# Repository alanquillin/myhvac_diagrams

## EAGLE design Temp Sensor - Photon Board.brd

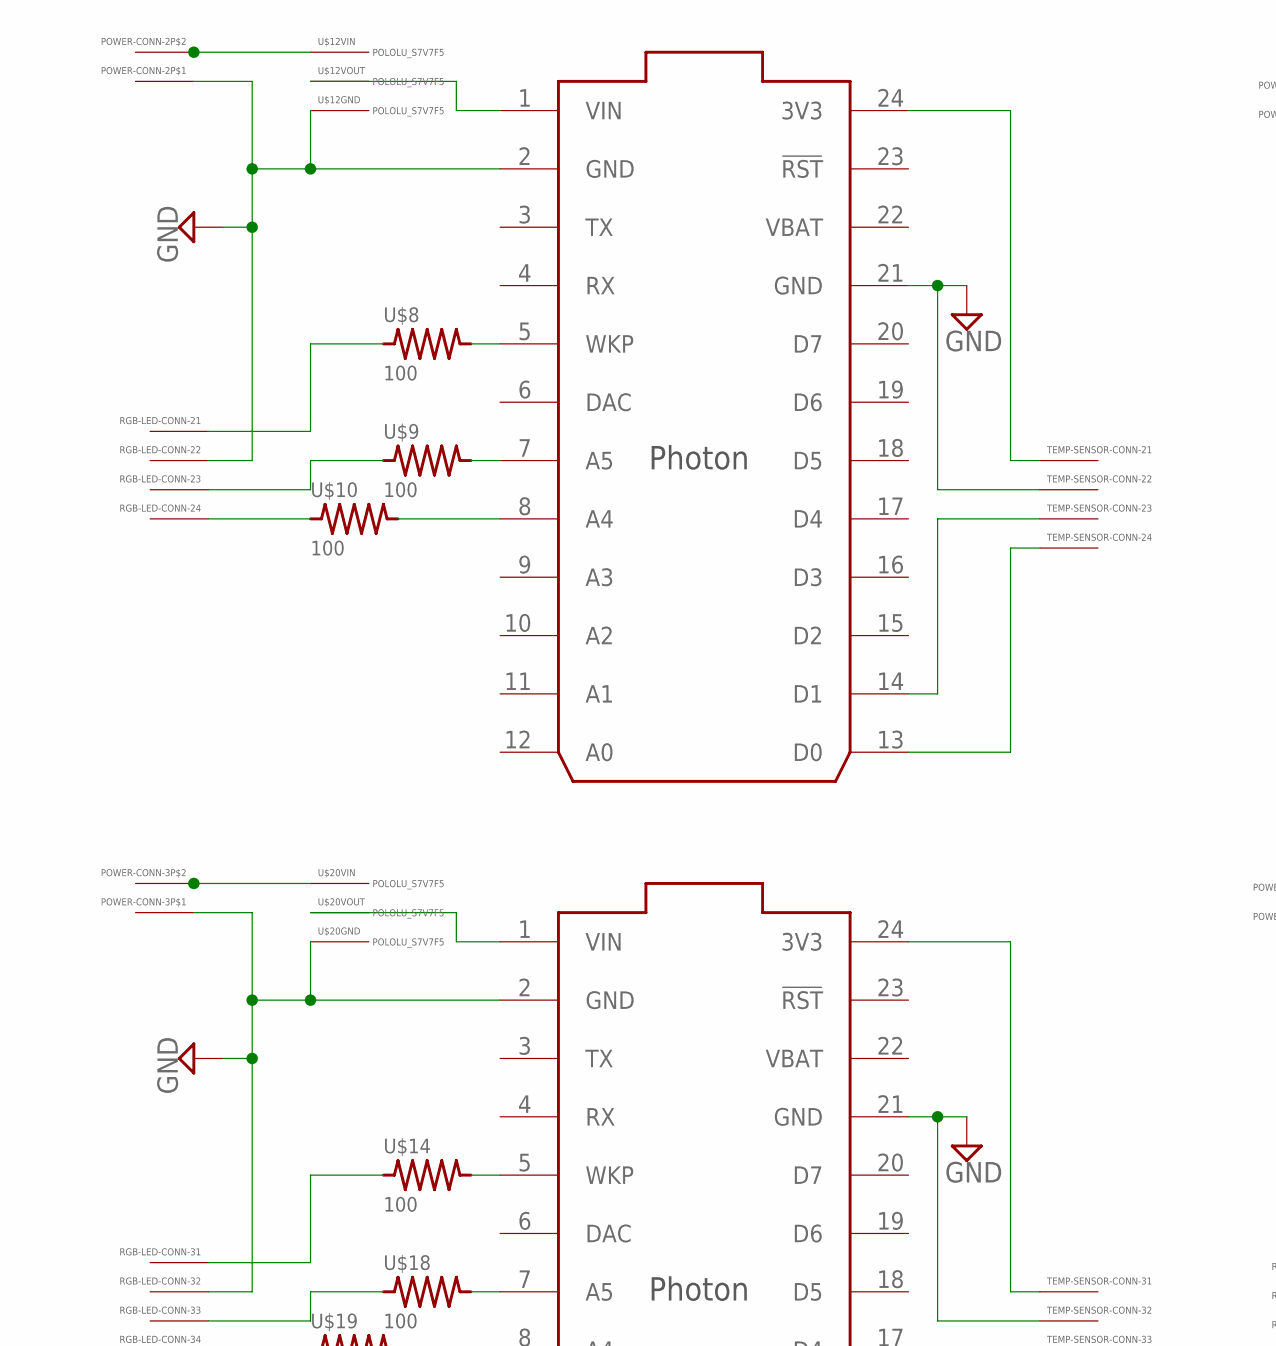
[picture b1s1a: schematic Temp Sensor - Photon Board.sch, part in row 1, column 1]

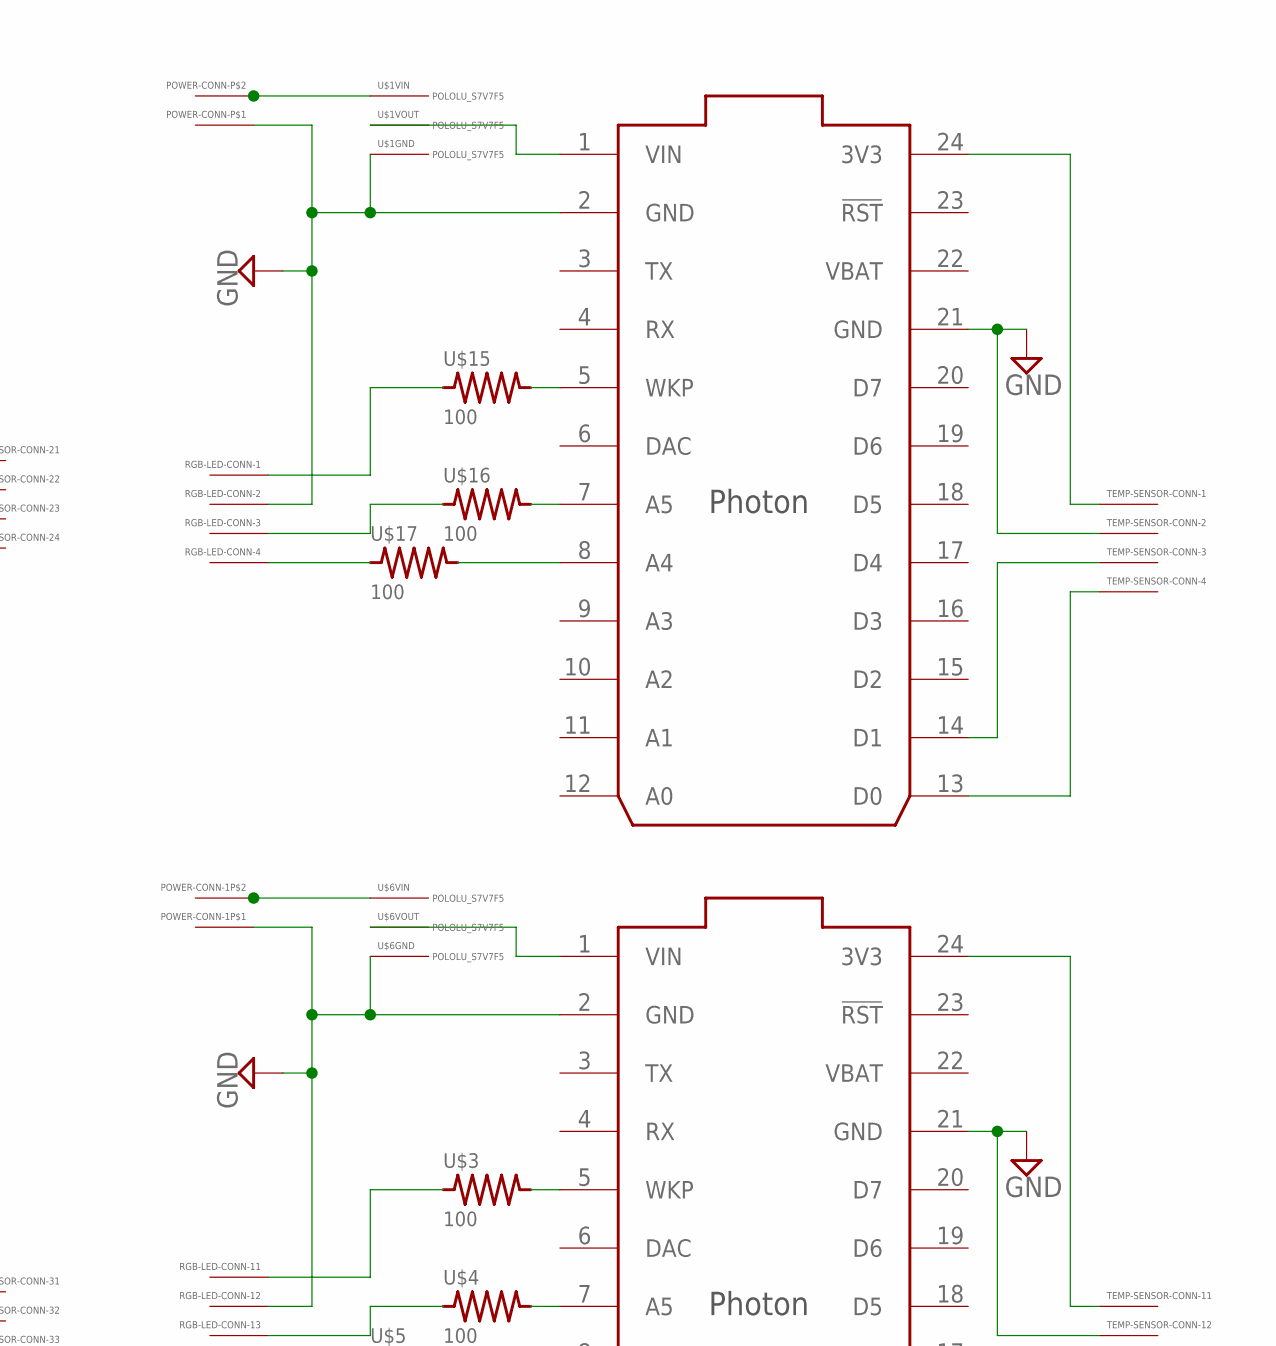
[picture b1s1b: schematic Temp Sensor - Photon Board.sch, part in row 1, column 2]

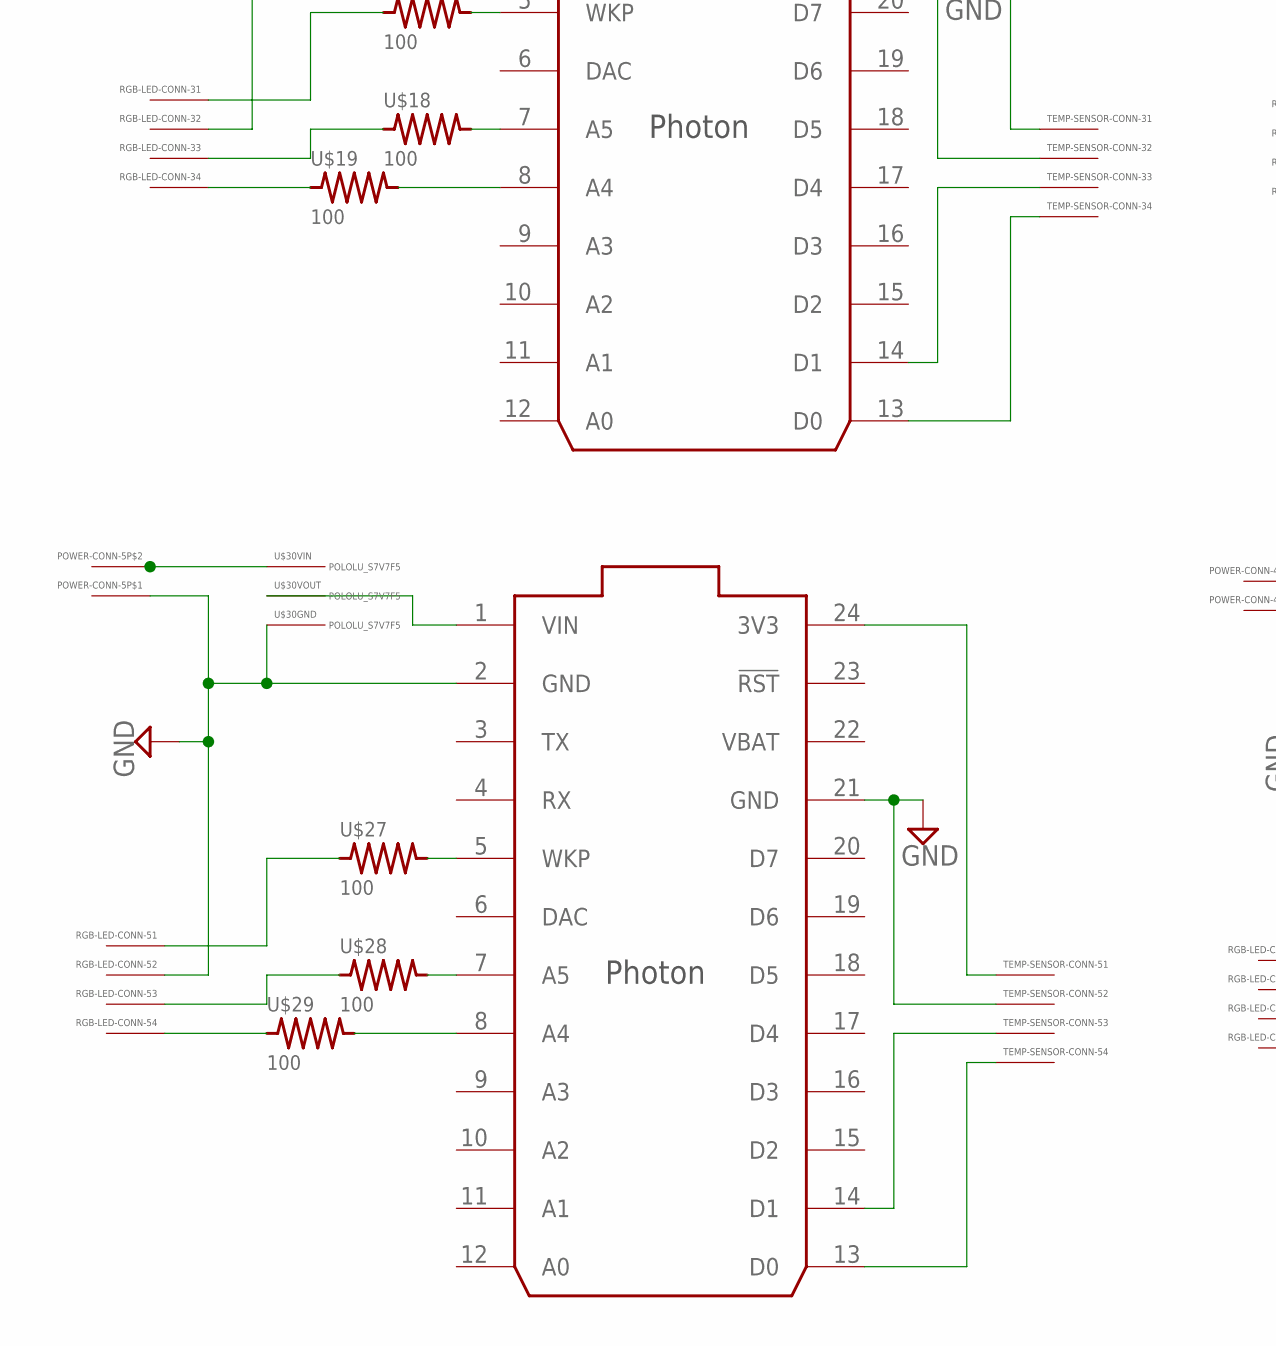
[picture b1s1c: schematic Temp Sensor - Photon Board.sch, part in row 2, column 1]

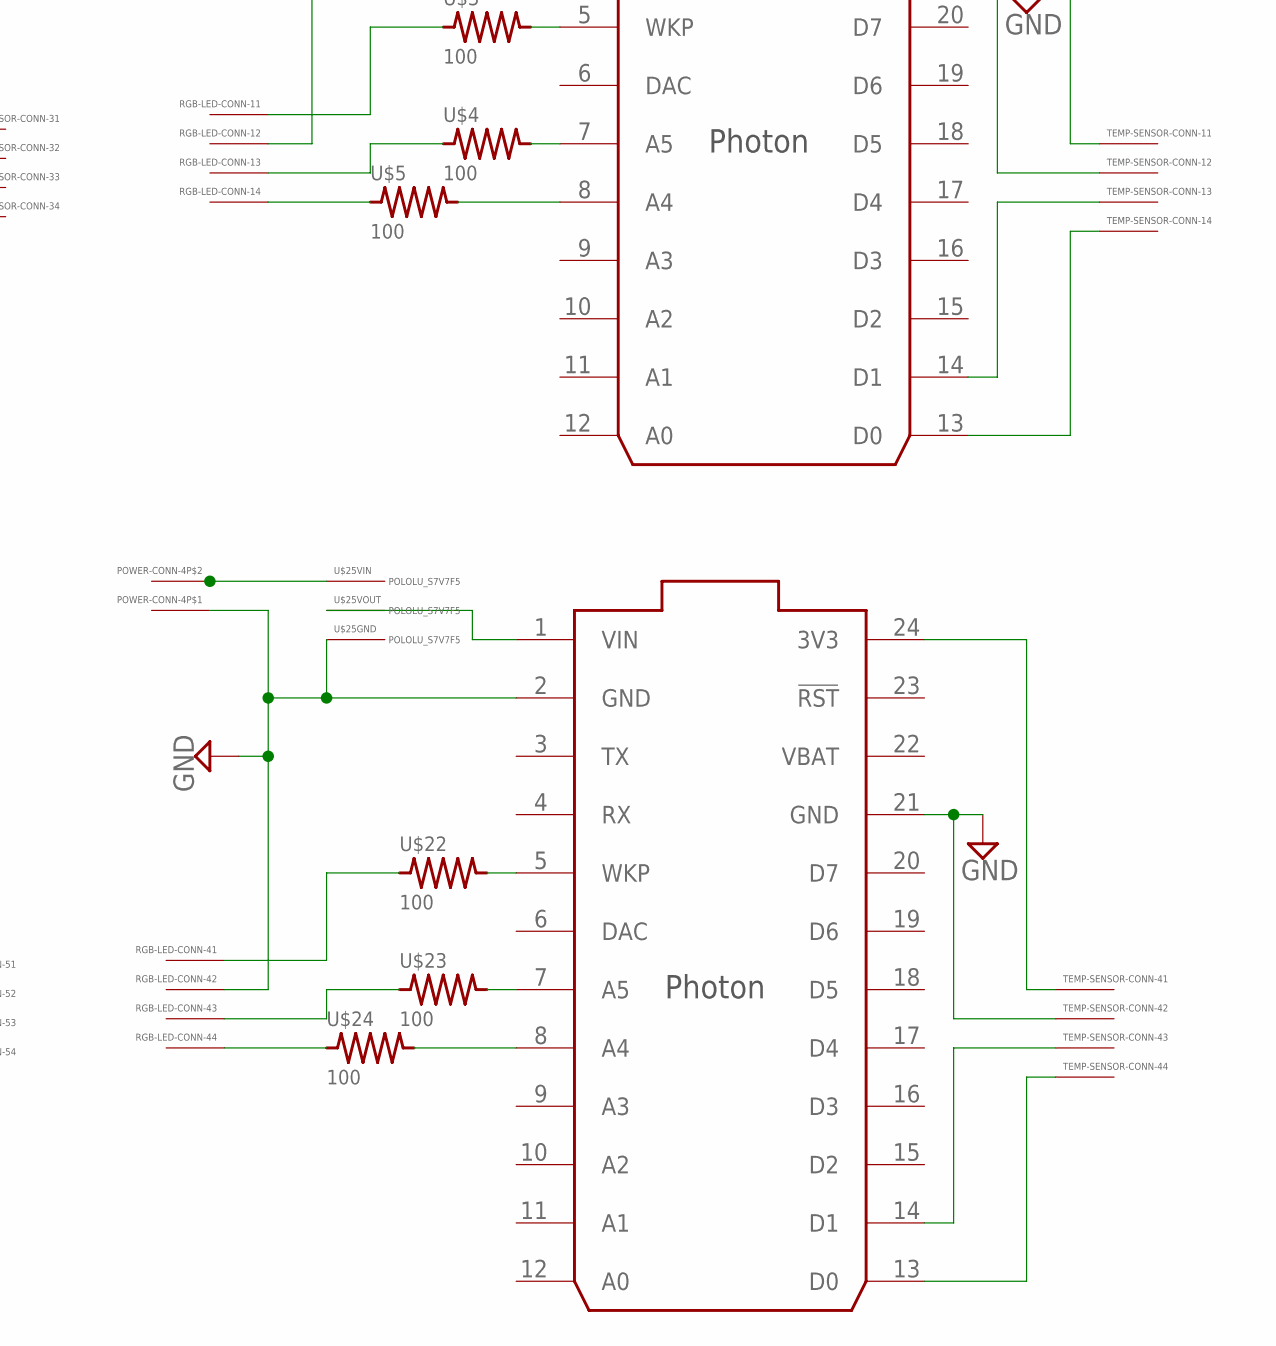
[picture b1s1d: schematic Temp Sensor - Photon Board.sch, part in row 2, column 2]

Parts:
POWER-CONN-, POWER-CONN-1, POWER-CONN-2, POWER-CONN-3, POWER-CONN-4, POWER-CONN-5: S2B-PH-K-S; JST_PH-2
RGB-LED-CONN-, RGB-LED-CONN-1, RGB-LED-CONN-2, RGB-LED-CONN-3, RGB-LED-CONN-4, RGB-LED-CONN-5: S4B-PH-K-S; JST_PH-4
TEMP-SENSOR-CONN-, TEMP-SENSOR-CONN-1, TEMP-SENSOR-CONN-2, TEMP-SENSOR-CONN-3, TEMP-SENSOR-CONN-4, TEMP-SENSOR-CONN-5: S4B-PH-K-S; JST_PH-4
U$1, U$6, U$12, U$20, U$25, U$30: POLOLU_S7V7F5; S7V7F5
U$2, U$7, U$11, U$13, U$21, U$26: Photon w/ Headers; PHOTON
U$3, U$4, U$5, U$8, U$9, U$10, U$14, U$15, U$16, U$17, U$18, U$19, U$22, U$23, U$24, U$27, U$28, U$29: 100; R0805

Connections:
GND: POWER-CONN-.P$1, POWER-CONN-1.P$1, POWER-CONN-2.P$1, POWER-CONN-3.P$1, POWER-CONN-4.P$1, POWER-CONN-5.P$1, RGB-LED-CONN-.P$2, RGB-LED-CONN-1.P$2, RGB-LED-CONN-2.P$2, RGB-LED-CONN-3.P$2, RGB-LED-CONN-4.P$2, RGB-LED-CONN-5.P$2, TEMP-SENSOR-CONN-.P$2, TEMP-SENSOR-CONN-1.P$2, TEMP-SENSOR-CONN-2.P$2, TEMP-SENSOR-CONN-3.P$2, TEMP-SENSOR-CONN-4.P$2, TEMP-SENSOR-CONN-5.P$2, U$1.GND, U$2.2 (GND), U$2.21 (GND), U$6.GND, U$7.2 (GND), U$7.21 (GND), U$11.2 (GND), U$11.21 (GND), U$12.GND, U$13.2 (GND), U$13.21 (GND), U$20.GND, U$21.2 (GND), U$21.21 (GND), U$25.GND, U$26.2 (GND), U$26.21 (GND), U$30.GND
unnamed: U$11.5 (WKP), U$15.2
unnamed: RGB-LED-CONN-.P$3, U$16.1
unnamed: RGB-LED-CONN-.P$4, U$17.1
unnamed: U$1.VOUT, U$11.1 (VIN)
unnamed: POWER-CONN-.P$2, U$1.VIN
unnamed: RGB-LED-CONN-1.P$3, U$4.1
unnamed: TEMP-SENSOR-CONN-.P$1, U$11.24 (3V3)
unnamed: TEMP-SENSOR-CONN-.P$3, U$11.14 (D1)
unnamed: TEMP-SENSOR-CONN-.P$4, U$11.13 (D0)
unnamed: RGB-LED-CONN-1.P$4, U$5.1
unnamed: U$11.7 (A5), U$16.2
unnamed: U$11.8 (A4), U$17.2
unnamed: RGB-LED-CONN-.P$1, U$15.1
unnamed: TEMP-SENSOR-CONN-1.P$1, U$2.24 (3V3)
unnamed: TEMP-SENSOR-CONN-1.P$3, U$2.14 (D1)
unnamed: TEMP-SENSOR-CONN-1.P$4, U$2.13 (D0)
unnamed: U$2.5 (WKP), U$3.2
unnamed: U$2.7 (A5), U$4.2
unnamed: U$2.8 (A4), U$5.2
unnamed: RGB-LED-CONN-1.P$1, U$3.1
unnamed: U$2.1 (VIN), U$6.VOUT
unnamed: POWER-CONN-1.P$2, U$6.VIN
unnamed: RGB-LED-CONN-2.P$3, U$9.1
unnamed: RGB-LED-CONN-2.P$4, U$10.1
unnamed: TEMP-SENSOR-CONN-2.P$1, U$7.24 (3V3)
unnamed: TEMP-SENSOR-CONN-2.P$3, U$7.14 (D1)
unnamed: TEMP-SENSOR-CONN-2.P$4, U$7.13 (D0)
unnamed: U$7.5 (WKP), U$8.2
unnamed: U$7.7 (A5), U$9.2
unnamed: U$7.8 (A4), U$10.2
unnamed: RGB-LED-CONN-2.P$1, U$8.1
unnamed: U$7.1 (VIN), U$12.VOUT
unnamed: POWER-CONN-2.P$2, U$12.VIN
unnamed: RGB-LED-CONN-3.P$3, U$18.1
unnamed: RGB-LED-CONN-3.P$4, U$19.1
unnamed: TEMP-SENSOR-CONN-3.P$1, U$13.24 (3V3)
unnamed: TEMP-SENSOR-CONN-3.P$3, U$13.14 (D1)
unnamed: TEMP-SENSOR-CONN-3.P$4, U$13.13 (D0)
unnamed: U$13.5 (WKP), U$14.2
unnamed: U$13.7 (A5), U$18.2
unnamed: U$13.8 (A4), U$19.2
unnamed: RGB-LED-CONN-3.P$1, U$14.1
unnamed: U$13.1 (VIN), U$20.VOUT
unnamed: POWER-CONN-3.P$2, U$20.VIN
unnamed: RGB-LED-CONN-4.P$3, U$23.1
unnamed: RGB-LED-CONN-4.P$4, U$24.1
unnamed: TEMP-SENSOR-CONN-4.P$1, U$21.24 (3V3)
unnamed: TEMP-SENSOR-CONN-4.P$3, U$21.14 (D1)
unnamed: TEMP-SENSOR-CONN-4.P$4, U$21.13 (D0)
unnamed: U$21.5 (WKP), U$22.2
unnamed: U$21.7 (A5), U$23.2
unnamed: U$21.8 (A4), U$24.2
unnamed: RGB-LED-CONN-4.P$1, U$22.1
unnamed: U$21.1 (VIN), U$25.VOUT
unnamed: POWER-CONN-4.P$2, U$25.VIN
unnamed: RGB-LED-CONN-5.P$3, U$28.1
unnamed: RGB-LED-CONN-5.P$4, U$29.1
unnamed: TEMP-SENSOR-CONN-5.P$1, U$26.24 (3V3)
unnamed: TEMP-SENSOR-CONN-5.P$3, U$26.14 (D1)
unnamed: TEMP-SENSOR-CONN-5.P$4, U$26.13 (D0)
unnamed: U$26.5 (WKP), U$27.2
unnamed: U$26.7 (A5), U$28.2
unnamed: U$26.8 (A4), U$29.2
unnamed: RGB-LED-CONN-5.P$1, U$27.1
unnamed: U$26.1 (VIN), U$30.VOUT
unnamed: POWER-CONN-5.P$2, U$30.VIN
VBAT: U$2.22 (VBAT), U$7.22 (VBAT), U$11.22 (VBAT), U$13.22 (VBAT), U$21.22 (VBAT), U$26.22 (VBAT)

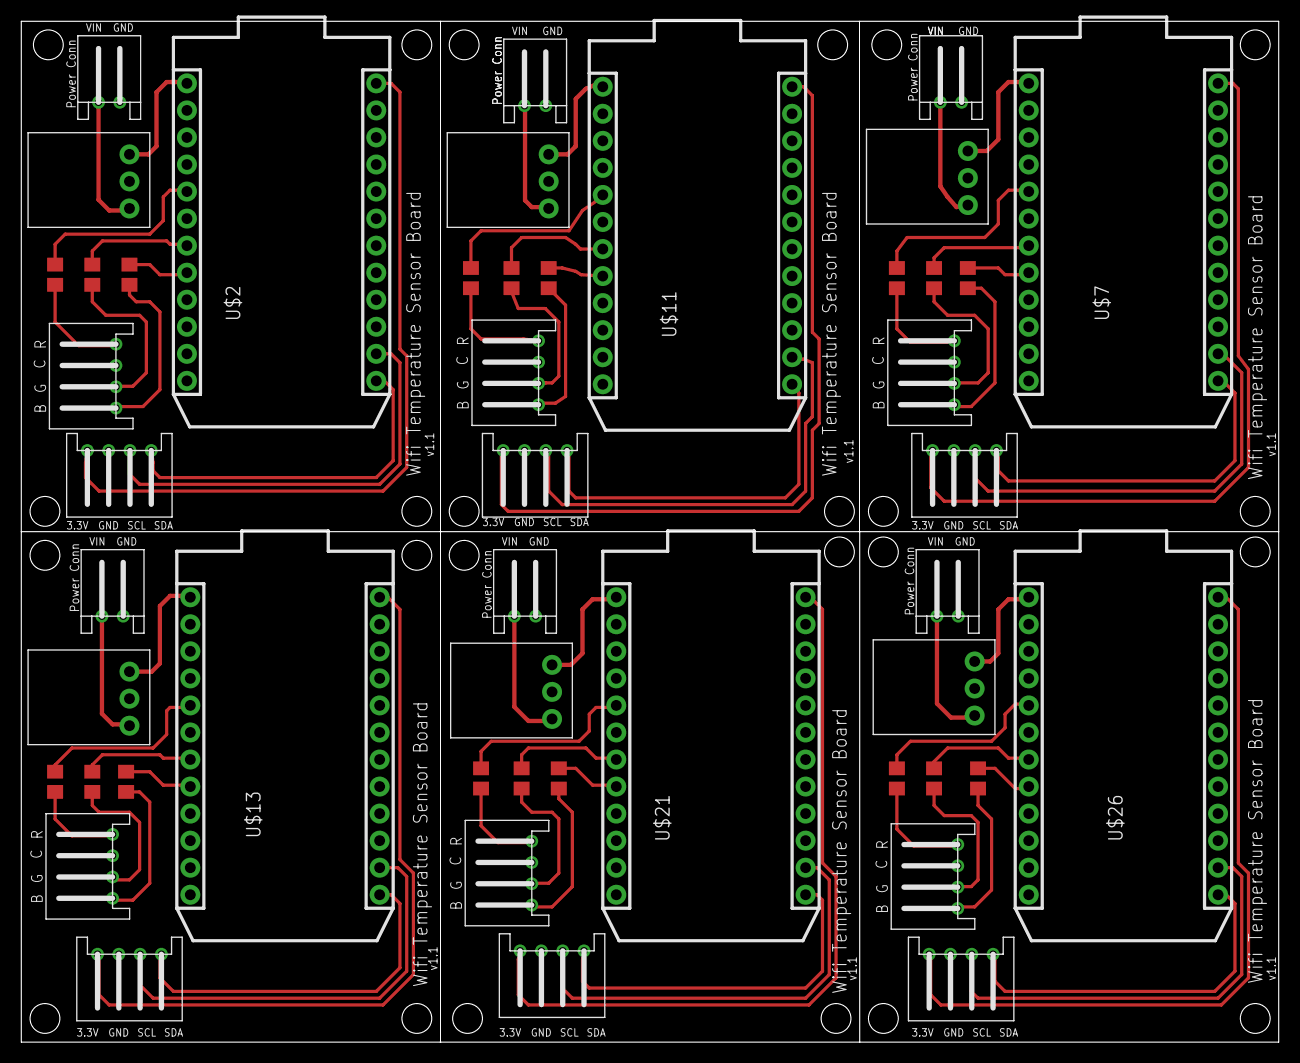
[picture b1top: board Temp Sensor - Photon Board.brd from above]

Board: 2 copper layers, 118.1 x 95.9 mm, 48 parts (0 on the bottom side), 68 nets.

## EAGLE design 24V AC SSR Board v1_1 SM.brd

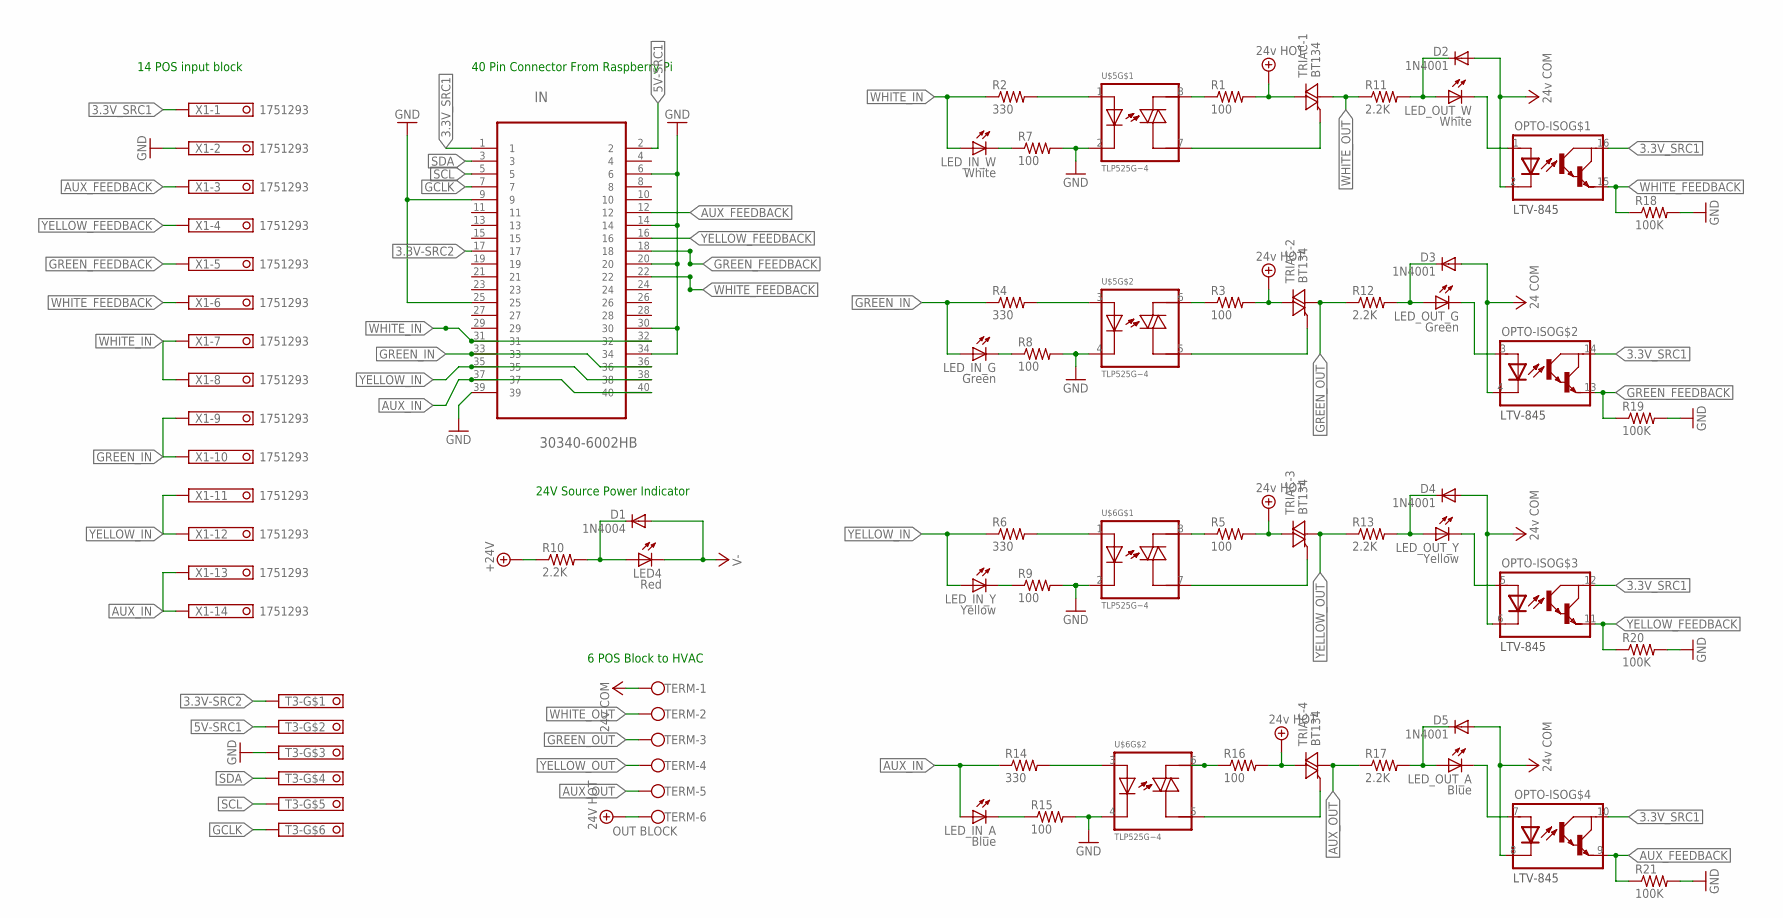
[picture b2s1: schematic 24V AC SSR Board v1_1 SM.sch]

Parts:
D1: 1N4004; DO41-10
D2, D3, D4, D5: 1N4001; DO41-10
IN: 30340-6002HB; 3M_2540-6002UB
LED4: Red; LED3MM
LED_IN_A: Blue; LED3MM
LED_IN_G: Green; LED3MM
LED_IN_W: White; LED3MM
LED_IN_Y: Yellow; LED3MM
LED_OUT_A: Blue; LED3MM
LED_OUT_G: Green; LED3MM
LED_OUT_W: White; LED3MM
LED_OUT_Y: Yellow; LED3MM
OPTO-ISO: LTV-845; DIL16
R1, R3, R5, R7, R8, R9, R15, R16: 100; 0204/7
R2, R4, R6, R14: 330; 0204/7
R10, R11, R12, R13, R17: 2.2K; 0204/7
R18, R19, R20, R21: 100K; 0204/7
T3-: 6-POS-SCREW-TERM-PT-3.5MM
TERM: OUT BLOCK; W237-6
TRIAC-1, TRIAC-2, TRIAC-3, TRIAC-4: BT134; SOT82
U$5, U$6: TLP525G−4; DIL08
X1: 1751293

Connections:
3.3V-SRC2: IN.17, T3-.1
3.3V_SRC1: IN.1, OPTO-ISO.10 (COLLECTOR), OPTO-ISO.12 (COLLECTOR), OPTO-ISO.14 (COLLECTOR), OPTO-ISO.16 (COLLECTOR), X1.1
5V-SRC1: IN.2, T3-.2
+24V: R1.2, R3.2, R5.2, R10.1, R16.2, TERM.6, TRIAC-1.2 (A2), TRIAC-2.2 (A2), TRIAC-3.2 (A2), TRIAC-4.2 (A2)
AUX_FEEDBACK: IN.12, OPTO-ISO.9 (EMITTER), R21.1, X1.3
AUX_IN: IN.37, IN.40, LED_IN_A.A, R14.1, X1.13, X1.14
AUX_OUT: R17.1, TERM.5, TRIAC-4.1 (A1)
GCLK: IN.7, T3-.6
GND: IN.6, IN.9, IN.14, IN.20, IN.25, IN.30, IN.34, IN.39, R7.2, R8.2, R9.2, R15.2, R18.2, R19.2, R20.2, R21.2, T3-.3, U$5.2 (CATHODE), U$5.4 (CATHODE), U$6.2 (CATHODE), U$6.4 (CATHODE), X1.2
GREEN_FEEDBACK: IN.18, OPTO-ISO.13 (EMITTER), R19.1, X1.5
GREEN_IN: IN.33, IN.36, LED_IN_G.A, R4.1, X1.9, X1.10
GREEN_OUT: R12.1, TERM.3, TRIAC-2.1 (A1)
unnamed: TRIAC-1.3 (G), U$5.7 (T1)
unnamed: R2.2, U$5.1 (ANNODE)
unnamed: TRIAC-4.3 (G), U$6.5 (T1)
unnamed: R1.1, U$5.8 (T2)
unnamed: TRIAC-3.3 (G), U$6.7 (T1)
unnamed: R4.2, U$5.3 (ANNODE)
unnamed: TRIAC-2.3 (G), U$5.5 (T1)
unnamed: R3.1, U$5.6 (T2)
unnamed: LED_OUT_W.K (C), OPTO-ISO.1 (ANNODE)
unnamed: R6.2, U$6.1 (ANNODE)
unnamed: LED_OUT_G.K (C), OPTO-ISO.3 (ANNODE)
unnamed: R5.1, U$6.8 (T2)
unnamed: LED_OUT_Y.K (C), OPTO-ISO.5 (ANNODE)
unnamed: LED_OUT_A.K (C), OPTO-ISO.7 (ANNODE)
unnamed: LED_IN_W.K (C), R7.1
unnamed: LED_IN_G.K (C), R8.1
unnamed: LED_IN_Y.K (C), R9.1
unnamed: D2.C, LED_OUT_W.A, R11.2
unnamed: D3.C, LED_OUT_G.A, R12.2
unnamed: D4.C, LED_OUT_Y.A, R13.2
unnamed: D1.C, LED4.A, R10.2
unnamed: R14.2, U$6.3 (ANNODE)
unnamed: LED_IN_A.K (C), R15.1
unnamed: R16.1, U$6.6 (T2)
unnamed: D5.C, LED_OUT_A.A, R17.2
SCL: IN.5, T3-.5
SDA: IN.3, T3-.4
V-: D1.A, D2.A, D3.A, D4.A, D5.A, LED4.K (C), OPTO-ISO.2 (CATHODE), OPTO-ISO.4 (CATHODE), OPTO-ISO.6 (CATHODE), OPTO-ISO.8 (CATHODE), TERM.1
WHITE_FEEDBACK: IN.22, OPTO-ISO.15 (EMITTER), R18.1, X1.6
WHITE_IN: IN.31, IN.32, LED_IN_W.A, R2.1, X1.7, X1.8
WHITE_OUT: R11.1, TERM.2, TRIAC-1.1 (A1)
YELLOW_FEEDBACK: IN.16, OPTO-ISO.11 (EMITTER), R20.1, X1.4
YELLOW_IN: IN.35, IN.38, LED_IN_Y.A, R6.1, X1.11, X1.12
YELLOW_OUT: R13.1, TERM.4, TRIAC-3.1 (A1)

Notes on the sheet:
40 Pin Connector From Raspberry Pi
6 POS Block to HVAC
24V Source Power Indicator
14 POS input block

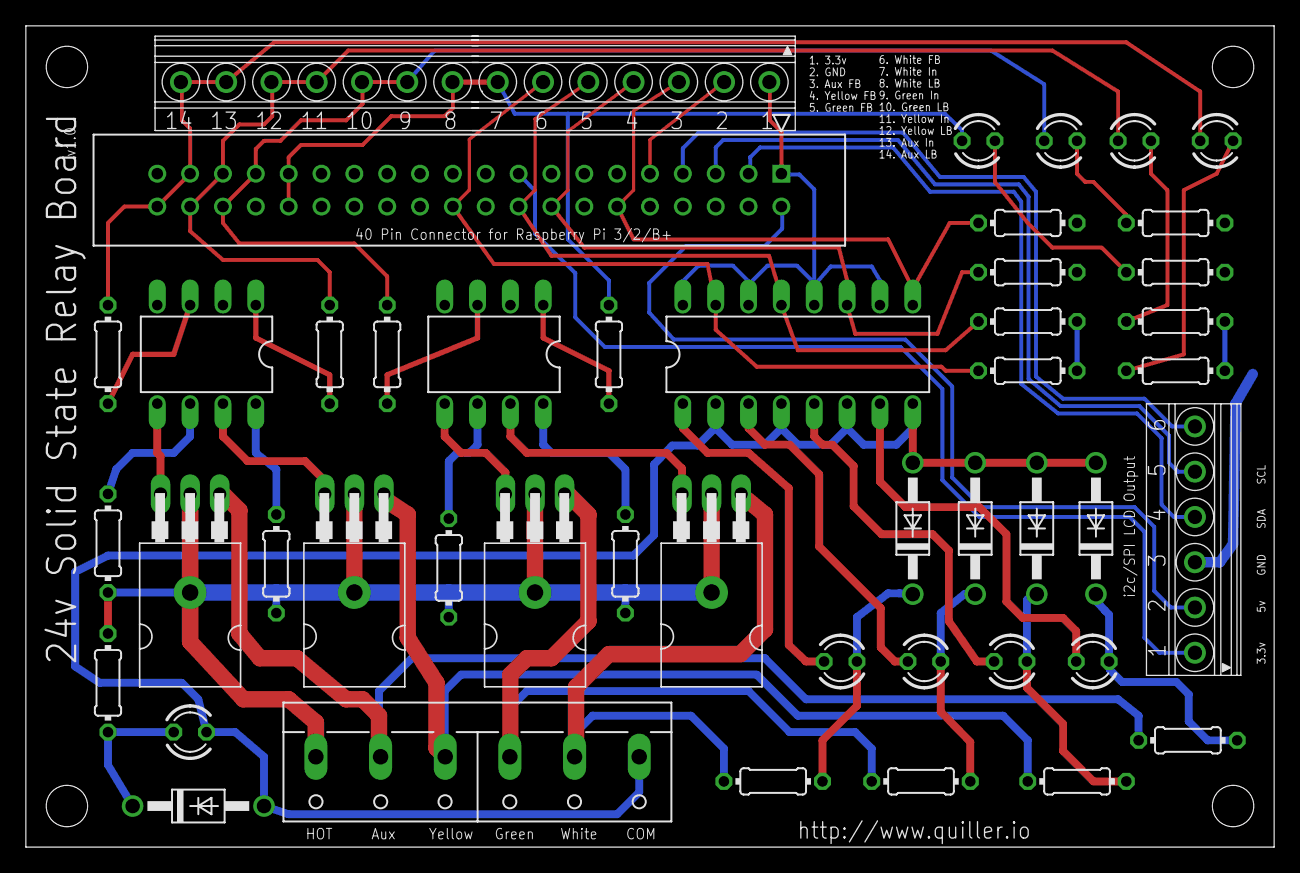
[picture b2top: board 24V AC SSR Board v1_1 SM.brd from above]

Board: 2 copper layers, 96.5 x 63.5 mm, 46 parts (0 on the bottom side), 46 nets.

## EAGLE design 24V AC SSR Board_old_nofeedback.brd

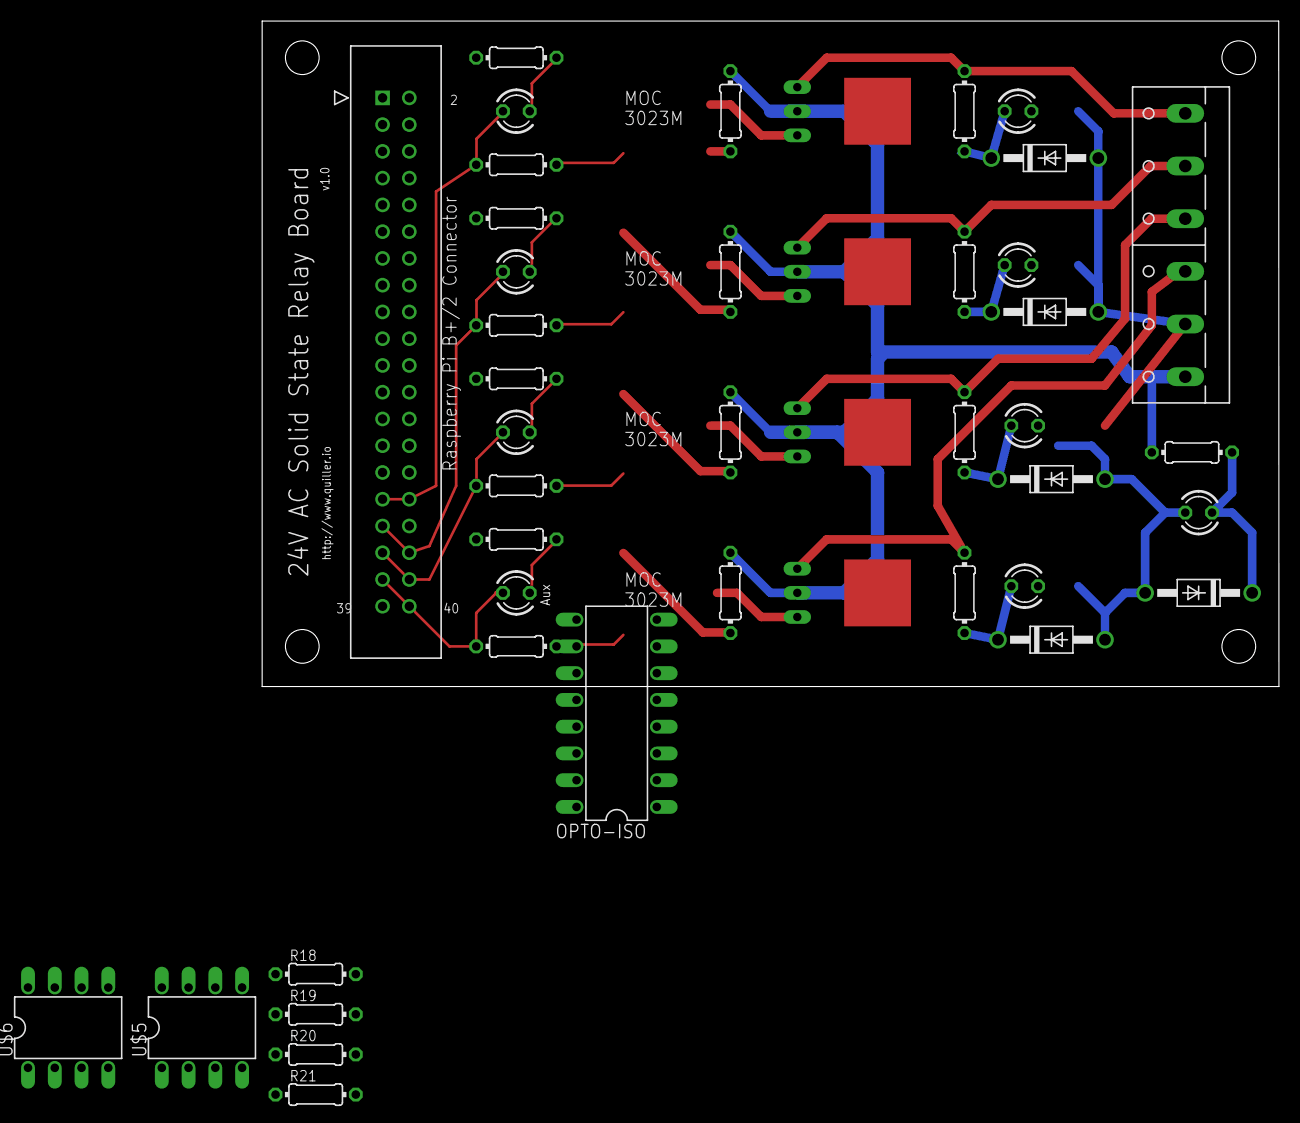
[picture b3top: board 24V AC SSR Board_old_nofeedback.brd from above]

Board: 2 copper layers, 96.5 x 63.2 mm, 44 parts (0 on the bottom side), 41 nets.

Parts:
D1: 1N4004; DO41-10
D2, D3, D4, D5: 1N4001; DO41-10
IN: 30340-6002HB; 3M_2540-6002UB
LED1, LED5: White; LED3MM
LED2, LED6: Green; LED3MM
LED3, LED7: Yellow; LED3MM
LED4: red; LED3MM
LED8, LED9: Blue; LED3MM
OPTO-ISO: LTV-845; DIL16
R1, R3, R5, R16: 100; 0204/7
R2, R4, R6, R14: 330; 0204/7
R7, R8, R9, R15: 56; 0204/7
R10, R11, R12, R13, R17: 2.2K; 0204/7
R18, R19, R20, R21: 4.7K; 0204/7
TERM: W237-6
U$1, U$2, U$3, U$4: BT134; SOT-82
U$5, U$6: TLP525G−4; DIL08

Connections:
3.3V_SOURCE: IN.1, OPTO-ISO.10, OPTO-ISO.12, OPTO-ISO.14, OPTO-ISO.16
+24V: R1.2, R3.2, R5.2, R10.1, R16.2, TERM.1, U$1.P$2, U$2.P$2, U$3.P$2, U$4.P$2
AUX_IN: IN.37, IN.40, LED8.A, R14.1
AUX_LOOPBACK: IN.22, OPTO-ISO.9, R21.1
AUX_OUT: R17.1, TERM.3, U$4.P$1
GND: IN.6, IN.9, IN.14, IN.20, IN.25, IN.30, IN.34, IN.39, R7.2, R8.2, R9.2, R15.2, R18.2, R19.2, R20.2, R21.2, U$5.2, U$5.4, U$6.2, U$6.4
GREEN_IN: IN.33, IN.36, LED2.A, R4.1
GREEN_LOOPBACK: IN.16, OPTO-ISO.13, R19.1
GREEN_OUT: R12.1, TERM.5, U$2.P$1
unnamed: U$1.P$3, U$5.7
unnamed: R2.2, U$5.1
unnamed: U$4.P$3, U$6.5
unnamed: R1.1, U$5.8
unnamed: U$3.P$3, U$6.7
unnamed: R4.2, U$5.3
unnamed: U$2.P$3, U$5.5
unnamed: R3.1, U$5.6
unnamed: LED5.K, OPTO-ISO.1
unnamed: R6.2, U$6.1
unnamed: LED6.K, OPTO-ISO.3
unnamed: R5.1, U$6.8
unnamed: LED7.K, OPTO-ISO.5
unnamed: LED9.K, OPTO-ISO.7
unnamed: LED1.K, R7.1
unnamed: LED2.K, R8.1
unnamed: LED3.K, R9.1
unnamed: D2.C, LED5.A, R11.2
unnamed: D3.C, LED6.A, R12.2
unnamed: D4.C, LED7.A, R13.2
unnamed: D1.C, LED4.A, R10.2
unnamed: R14.2, U$6.3
unnamed: LED8.K, R15.1
unnamed: R16.1, U$6.6
unnamed: D5.C, LED9.A, R17.2
V-: D1.A, D2.A, D3.A, D4.A, D5.A, LED4.K, OPTO-ISO.2, OPTO-ISO.4, OPTO-ISO.6, OPTO-ISO.8, TERM.2
WHITE_IN: IN.31, IN.32, LED1.A, R2.1
WHITE_LOOPBACK: IN.12, OPTO-ISO.15, R18.1
WHITE_OUT: R11.1, TERM.6, U$1.P$1
YELLOW_IN: IN.35, IN.38, LED3.A, R6.1
YELLOW_LOOPBACK: IN.18, OPTO-ISO.11, R20.1
YELLOW_OUT: R13.1, TERM.4, U$3.P$1

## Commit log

2016-02-06 Added new opto-isolators and new custome library
2016-02-09 Cleaned the board layout
2016-03-09 Added Photon Board schematics and board
2016-03-20 Added Temp Sensor gerber files. General cleanup or bck files
2016-05-21 Modified the temp sensor to use a prebuilt power converter
